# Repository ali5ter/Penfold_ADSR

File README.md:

> **⚠️ Archived 2025-08-25. No longer maintained.**

# Penfold_ADSR
[KiCad](https://www.kicad.org/) project for the circuit and PCB of R.A. Penfolds ADSR design which I adapted as a Eurorack powered module.
The original circuit is taken from [the book, "Electronic Synthesiser Construction" by R. A. Penfold](https://sdiy.info/wiki/Penfold_synthesiser), published by Babani in 1986.

I have kept to the original design as much as possible but added power and switched INT.Gate via [a Eurorack spec bus](https://doepfer.de/home_e.htm).

I have yet to manufacture and test this circuit.

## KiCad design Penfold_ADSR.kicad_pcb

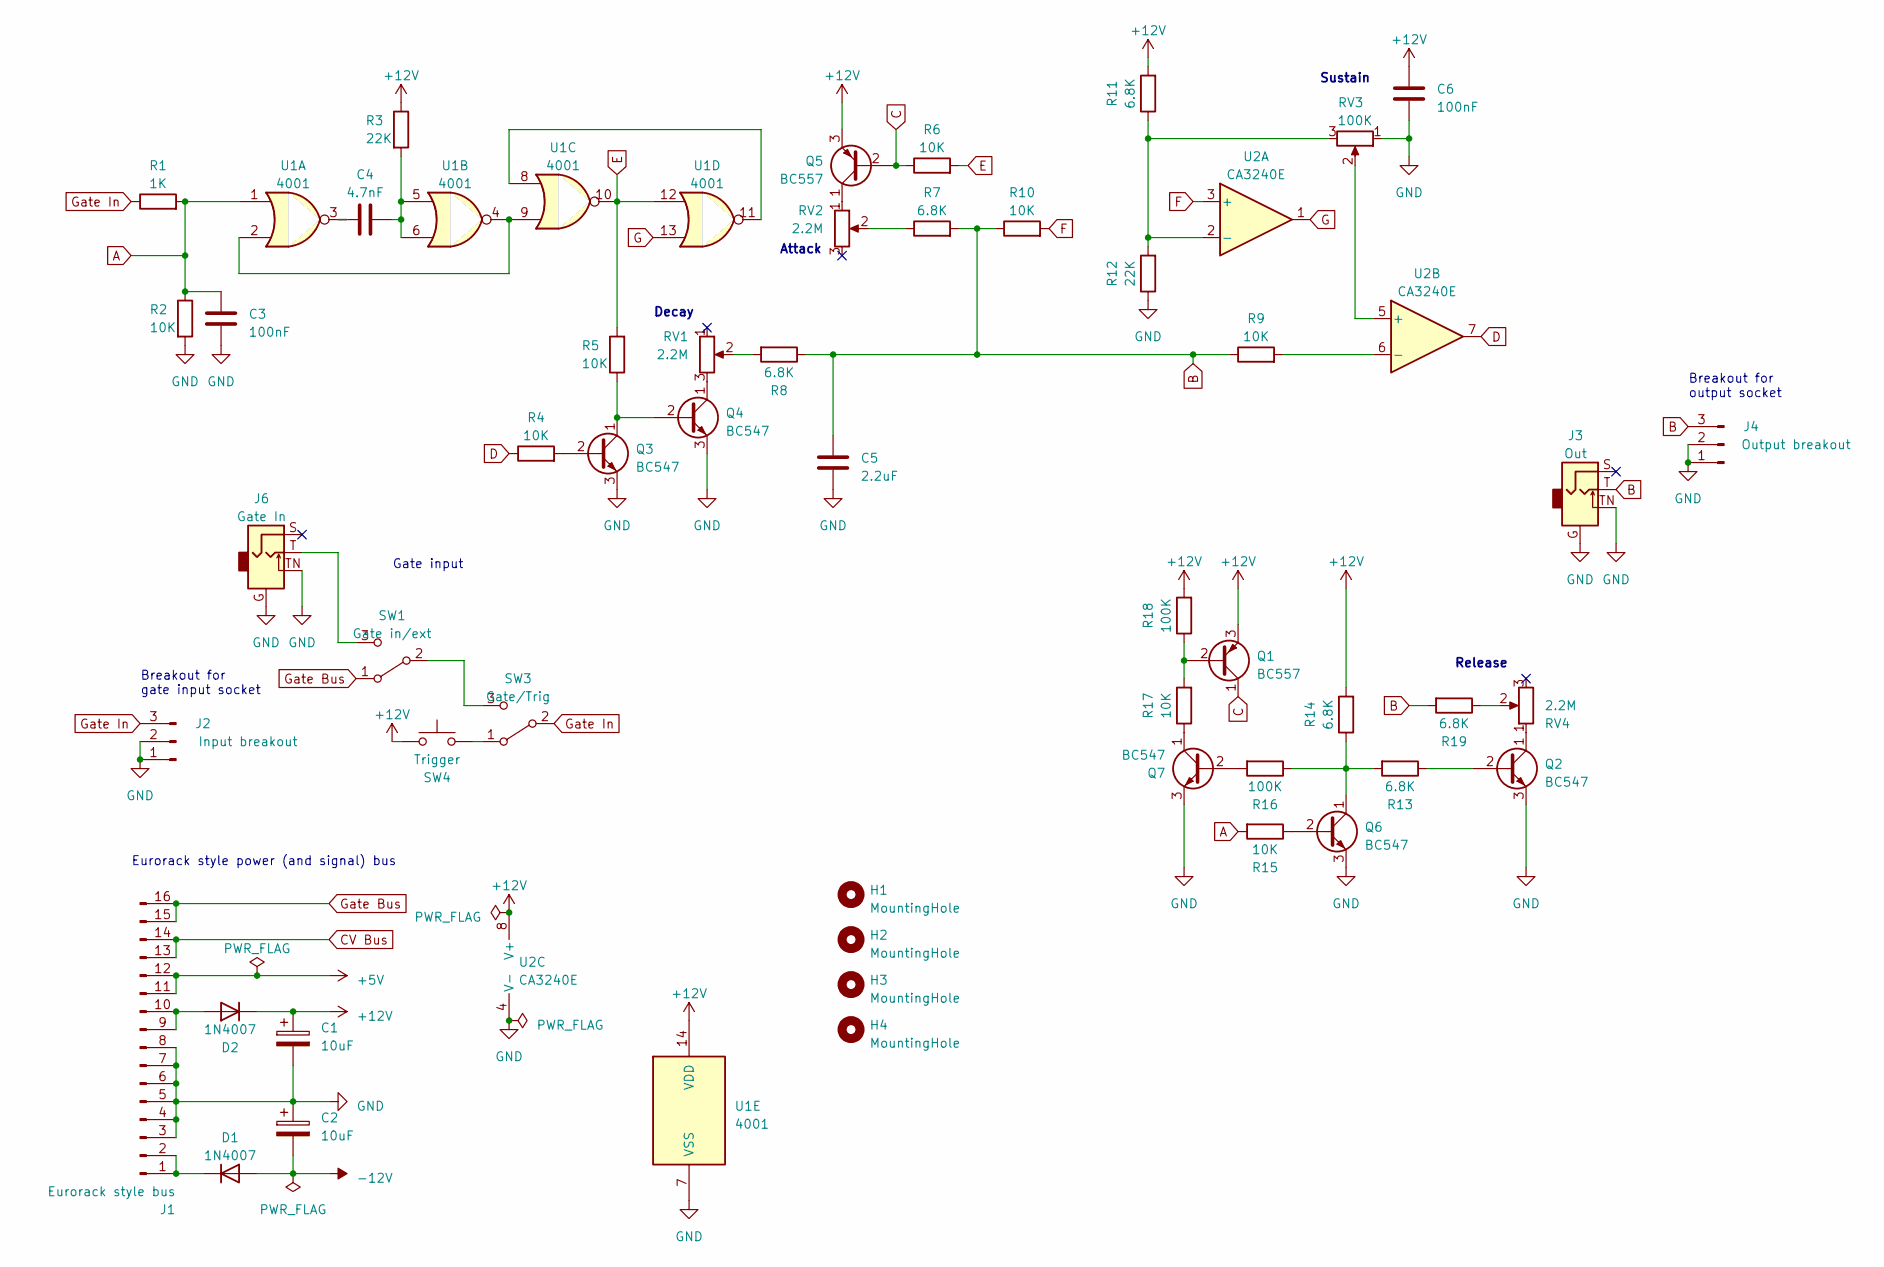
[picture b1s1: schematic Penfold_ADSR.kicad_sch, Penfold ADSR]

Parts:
C1, C2: 10uF; CP_Radial_D5.0mm_P2.00mm
C3, C6: 100nF; C_Disc_D5.0mm_W2.5mm_P5.00mm
C4: 4.7nF; C_Disc_D5.0mm_W2.5mm_P2.50mm
C5: 2.2uF; C_Disc_D5.0mm_W2.5mm_P2.50mm
D1, D2: 1N4007; D_DO-41_SOD81_P10.16mm_Horizontal
H1, H2, H3, H4: MountingHole; MountingHole_3.2mm_M3
J1: Eurorack style bus; PinHeader_2x08_P2.54mm_Vertical
J2: Input breakout; PinHeader_1x03_P2.54mm_Vertical
J3: Out
J4: Output breakout; PinHeader_1x03_P2.54mm_Vertical
J6: Gate In
Q1, Q5: BC557; TO-92_Inline
Q2, Q3, Q4, Q6, Q7: BC547; TO-92_Inline
R1: 1K; R_Axial_DIN0207_L6.3mm_D2.5mm_P10.16mm_Horizontal
R2, R4, R5, R6, R9, R10, R15, R17: 10K; R_Axial_DIN0207_L6.3mm_D2.5mm_P10.16mm_Horizontal
R3, R12: 22K; R_Axial_DIN0207_L6.3mm_D2.5mm_P10.16mm_Horizontal
R7, R8, R11, R13, R14, R19: 6.8K; R_Axial_DIN0207_L6.3mm_D2.5mm_P10.16mm_Horizontal
R16, R18: 100K; R_Axial_DIN0207_L6.3mm_D2.5mm_P10.16mm_Horizontal
RV1, RV2, RV4: 2.2M; PinHeader_1x03_P2.54mm_Vertical
RV3: 100K; PinHeader_1x03_P2.54mm_Vertical
SW1: Gate in/ext
SW3: Gate/Trig
SW4: Trigger
U1: 4001; DIP-14_W7.62mm_LongPads
U2: CA3240E; DIP-8_W7.62mm_LongPads

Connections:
+5V: J1.11, J1.12
+12V: C1.1, C6.2, D2.1 (K), Q1.3 (E), Q5.3 (E), R3.1, R11.2, R14.2, R18.2, SW4.1, U1.14 (VDD), U2.8 (V+)
-12V: C2.2, D1.2 (A)
A: C3.1, R1.2, R2.1, R15.2, U1.1
B: C5.2, J3.T, J4.3, R7.2, R8.1, R9.1, R10.1, R19.2
C: Q1.1 (C), Q5.2 (B), R6.1
CV Bus: J1.13, J1.14
D: R4.1, U2.7
E: R5.2, R6.2, U1.10, U1.12
F: R10.2, U2.3 (+)
G: U1.13, U2.1
GND: C1.2, C2.1, C3.2, C5.1, C6.1, J1.3, J1.4, J1.5, J1.6, J1.7, J1.8, J2.1, J2.2, J3.G, J3.TN, J4.1, J4.2, J6.G, J6.TN, Q2.3 (E), Q3.3 (E), Q4.3 (E), Q6.3 (E), Q7.3 (E), R2.2, R12.1, RV3.1, U1.7 (VSS), U2.4 (V-)
Gate Bus: J1.15, J1.16, SW1.1 (A)
Gate In: J2.3, R1.1, SW3.2 (B)
unnamed: C4.1, U1.3
unnamed: C4.2, R3.2, U1.5, U1.6
unnamed: D1.1 (K), J1.1, J1.2
unnamed: D2.2 (A), J1.9, J1.10
unnamed: J6.T, SW1.3 (C)
unnamed: Q1.2 (B), R17.2, R18.1
unnamed: Q2.2 (B), R13.1
unnamed: Q2.1 (C), RV4.1
unnamed: Q3.2 (B), R4.2
unnamed: Q3.1 (C), Q4.2 (B), R5.1
unnamed: Q4.1 (C), RV1.3
unnamed: Q5.1 (C), RV2.1
unnamed: Q6.2 (B), R15.1
unnamed: Q6.1 (C), R13.2, R14.1, R16.1
unnamed: Q7.2 (B), R16.2
unnamed: Q7.1 (C), R17.1
unnamed: R7.1, RV2.2
unnamed: R8.2, RV1.2
unnamed: R19.1, RV4.2
unnamed: SW1.2 (B), SW3.3 (C)
unnamed: SW3.1 (A), SW4.2
unnamed: U1.2, U1.4, U1.9
unnamed: U1.8, U1.11
unnamed: R11.1, R12.2, RV3.3, U2.2 (-)
unnamed: RV3.2, U2.5 (+)
unnamed: R9.2, U2.6 (-)

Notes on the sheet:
Attack
Decay
Eurorack style power (and signal) bus
Breakout for output socket
Breakout for gate input socket
Release
Sustain
Gate input

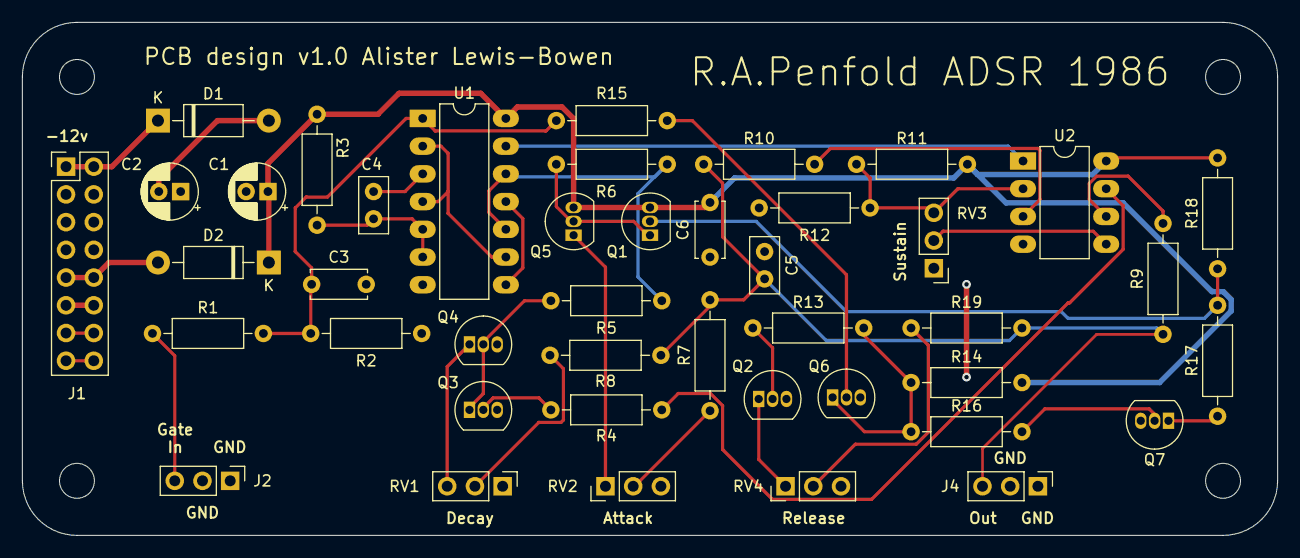
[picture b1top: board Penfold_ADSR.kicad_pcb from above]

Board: 2 copper layers, 115.0 x 47.0 mm, 47 parts (0 on the bottom side), 37 nets.

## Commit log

2023-07-04 after manufacture
2025-08-21 docs: sync archive banner
